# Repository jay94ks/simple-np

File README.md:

# Simple Number Pad

### License
* This repository: MIT, partially GPL-v3 due to TFT library.
* TFT library: GPL-v3, [ST7735_TFT_PICO](https://github.com/gavinlyonsrepo/ST7735_TFT_PICO)

### Video

### Schematic

See `hw/pdf/*.pdf` files to read more details.

### Features
* MCU: RP2040, 133MHz Dual core.
* 5 keys for user-defined functions.
* 17 keys for number pad.
* `TFT` display for calculator if no `HID` attached.
* 2 macro control keys, `RECORD` and `PLAY`.

### Plans for future features
* A flash memory to store user configurations? (currently, they're stored at `SRAM` of MCU only, so, volatile)
* I2C or SPI extension port?
* A little game that runs on the `TFT` display?
* Anything else...

### Firmware
Current planed features are implemented.
Now, calculator mode will be implemented soon.

### `tinyusb` RX callback.
Don't use `0.15.0` distribution that included on `pico-sdk`.
Update its branch to above version, then it works perfectly.

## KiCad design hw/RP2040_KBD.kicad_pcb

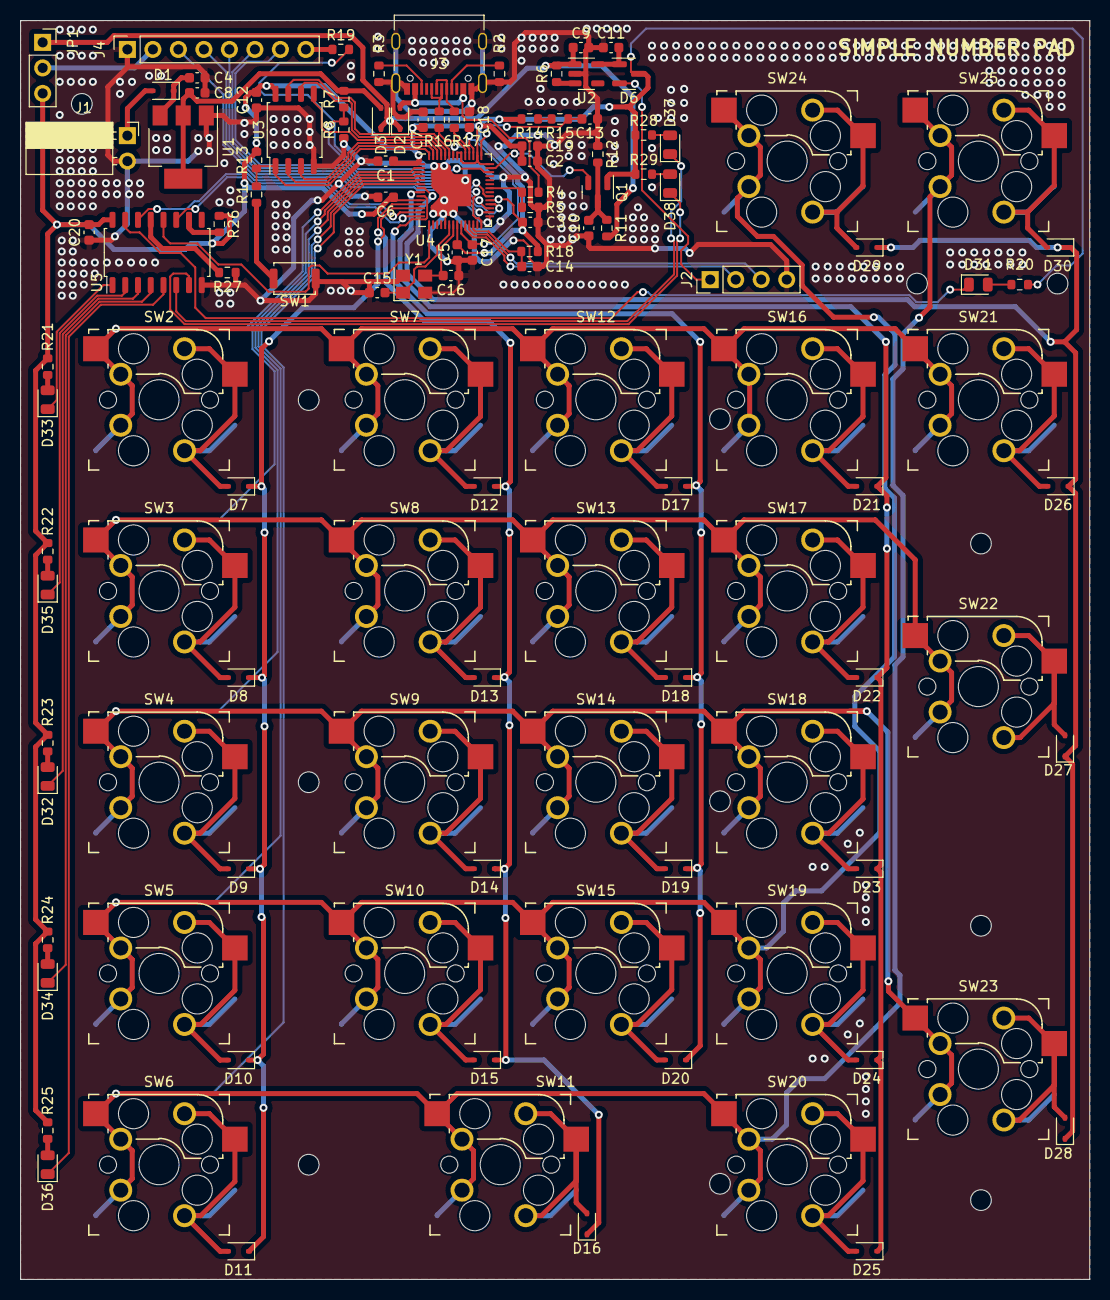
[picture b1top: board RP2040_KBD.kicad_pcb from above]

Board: 2 copper layers, 106.5 x 125.4 mm, 120 parts (0 on the bottom side), 98 nets.

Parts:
C1, C2, C3, C5, C6, C7, C12, C14, C20: 100nF; C_0603_1608Metric
C4, C8, C9, C11: 10uF; C_0603_1608Metric
C10: 1nF; C_0603_1608Metric
C13, C17, C18, C19: 2.2uF; C_0603_1608Metric
C15, C16: 26pF; C_0603_1608Metric
D1, D2, D3: 1N5819WS; D_SOD-323
D6: BAT54C; SOT-23
D7, D8, D9, D10, D11, D12, D13, D14, D15, D16, D17, D18, D19, D20, D21, D22, D23, D24, D25, D26, D27, D28, D29, D30: 1N4148WS; D_SOD-323
D31, D32, D33, D34, D35, D36, D37, D38: LED; LED_0805_2012Metric
J1: BAT_9V; PinSocket_1x02_P2.54mm_Horizontal
J2: SWD; PinHeader_1x04_P2.54mm_Vertical
J3: USB_C_Receptacle_USB2.0; USB_C_Receptacle_Palconn_UTC16-G
J4: TFT_LCD; PinSocket_1x08_P2.54mm_Vertical
JP1: TFT_VCC_SEL; PinSocket_1x03_P2.54mm_Vertical
Q1: 2N7002; SOT-23
R1, R5, R8, R13, R18, R26, R27: 10k; R_0603_1608Metric
R2, R3: 5.1k; R_0603_1608Metric
R4, R7: 5.6k; R_0603_1608Metric
R6, R12: 100k; R_0603_1608Metric
R11: 200k; R_0603_1608Metric
R14: 200; R_0603_1608Metric
R15: 1; R_0603_1608Metric
R16, R17: 6.8; R_0603_1608Metric
R19: 100; R_0603_1608Metric
R20, R21, R22, R23, R24, R25, R28, R29: 1k; R_0603_1608Metric
SW1: SW_Push; SW_Push_SPST_NO_Alps_SKRK
SW2, SW3, SW4, SW5, SW6, SW7, SW8, SW9, SW10, SW11, SW12, SW13, SW14, SW15, SW16, SW17, SW18, SW19, SW20, SW21, SW22, SW23, SW24, SW25: Kailh_socket_MX_optional_reversible
U1: AMS1117-5.0; SOT-223-3_TabPin2
U2: XC6220B331MR; SOT-23-5
U3: W25Q128JVSS; SOIC-8_5.23x5.23mm_P1.27mm
U4: RP2040; QFN-56-1EP_7x7mm_P0.4mm_EP3.2x3.2mm
U5: 74HC595; SOP-16_4.55x10.3mm_P1.27mm
Y1: 12MHz; Crystal_SMD_3225-4Pin_3.2x2.5mm

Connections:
+1V1: C17.2, C18.2, U4.23 (DVDD), U4.45 (VREG_VOUT), U4.50 (DVDD)
+3V3: C1.1, C2.1, C3.1, C5.1, C6.1, C7.1, C12.1, C19.1, C20.2, D6.3, JP1.3 (B), Q1.1 (G), R13.1, R14.1, R18.2, R20.1, R21.1, R22.1, R23.1, R24.1, R25.1, R26.1, R28.1, R29.1, U3.8 (VCC), U4.1 (IOVDD), U4.10 (IOVDD), U4.22 (IOVDD), U4.33 (IOVDD), U4.42 (IOVDD), U4.44 (VREG_IN), U4.48 (USB_VDD), U4.49 (IOVDD), U5.16 (VCC)
+5V: C9.1, D2.1 (K), D3.1 (K), JP1.1 (A), R6.2, R11.2, U2.1 (VIN)
+BATT: C4.1, D1.1 (K), U1.3 (VI)
/MCU/ADC_AVDD: C13.2, R15.2, U4.43 (ADC_AVDD)
/MCU/ADC_VREF: R14.2, R15.1
/MCU/GPIO22: R7.1, R8.2, U4.34 (GPIO22)
/MCU/GPIO24: R4.1, R5.2, U4.36 (GPIO24)
/MCU/GPIO29_ADC3: Q1.2 (S), U4.41 (GPIO29_ADC3)
/MCU/QSPI_SCLK: U3.6 (CLK), U4.52 (QSPI_SCLK)
/MCU/QSPI_SD0: U3.5 (DI(IO0)), U4.53 (QSPI_SD0)
/MCU/QSPI_SD1: U3.2 (DO(IO1)), U4.55 (QSPI_SD1)
/MCU/QSPI_SD2: U3.3 (IO2), U4.54 (QSPI_SD2)
/MCU/QSPI_SD3: U3.7 (IO3), U4.51 (QSPI_SD3)
/MCU/QSPI_SS: R1.1, R13.2, U3.1 (~CS), U4.56 (QSPI_SS)
/MCU/USB_DM: J3.A7 (D-), J3.B7 (D-), R17.1
/MCU/USB_DP: J3.A6 (D+), J3.B6 (D+), R16.1
/TFT_ST7735/TFT_BLK: J4.8, R19.1
/TFT_ST7735/TFT_VCC: J4.2, JP1.2 (C)
BAT_5V: C8.1, D3.2 (A), R7.2, U1.2 (VO)
C5: D26.1 (K), D27.1 (K), D28.1 (K), D29.1 (K), D30.1 (K), U4.7 (GPIO5)
GND: C1.2, C2.2, C3.2, C4.2, C5.2, C6.2, C7.2, C8.2, C9.2, C10.1, C11.1, C12.2, C13.1, C14.2, C15.1, C16.1, C17.1, C18.1, C19.2, C20.1, J1.2, J2.4, J3.A1 (GND), J3.A12 (GND), J3.B1 (GND), J3.B12 (GND), J3.S1 (SHIELD), J4.1, R2.2, R3.1, R5.1, R8.1, R12.1, R27.1, SW1.1, U1.1 (GND), U2.2 (GND), U3.4 (GND), U4.19 (TESTEN), U4.57 (GND), U5.8 (GND), Y1.2, Y1.4
GP0: SW2.1, SW7.1, SW12.1, SW16.1, SW21.1, U4.2 (GPIO0)
GP1: SW3.1, SW8.1, SW13.1, SW17.1, SW22.1, U4.3 (GPIO1)
GP2: SW4.1, SW9.1, SW14.1, SW18.1, SW23.1, U4.4 (GPIO2)
GP3: SW5.1, SW10.1, SW15.1, SW19.1, SW24.1, U4.5 (GPIO3)
GP4: SW6.1, SW11.1, SW20.1, SW25.1, U4.6 (GPIO4)
GP6: D21.1 (K), D22.1 (K), D23.1 (K), D24.1 (K), D25.1 (K), U4.8 (GPIO6)
GP7: D17.1 (K), D18.1 (K), D19.1 (K), D20.1 (K), U4.9 (GPIO7)
GP8: D12.1 (K), D13.1 (K), D14.1 (K), D15.1 (K), D16.1 (K), U4.11 (GPIO8)
GP9: D7.1 (K), D8.1 (K), D9.1 (K), D10.1 (K), D11.1 (K), U4.12 (GPIO9)
GP10: U4.13 (GPIO10), U5.14 (SER)
GP11: U4.14 (GPIO11), U5.11 (SRCLK)
GP12: U4.15 (GPIO12), U5.12 (RCLK)
GP17: J4.7, U4.28 (GPIO17)
GP18: J4.3, U4.29 (GPIO18)
GP19: J4.4, U4.30 (GPIO19)
GP20: J4.6, U4.31 (GPIO20)
GP21: J4.5, U4.32 (GPIO21)
GP28: R19.2, U4.40 (GPIO28_ADC2)
unnamed: D1.2 (A), J1.1
unnamed: D7.2 (A), SW2.2
unnamed: D8.2 (A), SW3.2
unnamed: D9.2 (A), SW4.2
unnamed: D10.2 (A), SW5.2
unnamed: D11.2 (A), SW6.2
unnamed: D12.2 (A), SW7.2
unnamed: D13.2 (A), SW8.2
unnamed: D14.2 (A), SW9.2
unnamed: D15.2 (A), SW10.2
unnamed: D16.2 (A), SW11.2
unnamed: D17.2 (A), SW12.2
unnamed: D18.2 (A), SW13.2
unnamed: D19.2 (A), SW14.2
unnamed: D20.2 (A), SW15.2
unnamed: D21.2 (A), SW16.2
unnamed: D22.2 (A), SW17.2
unnamed: D23.2 (A), SW18.2
unnamed: D24.2 (A), SW19.2
unnamed: D25.2 (A), SW20.2
unnamed: D26.2 (A), SW21.2
unnamed: D27.2 (A), SW22.2
unnamed: D28.2 (A), SW23.2
unnamed: D29.2 (A), SW24.2
unnamed: D30.2 (A), SW25.2
unnamed: D31.2 (A), R20.2
unnamed: D31.1 (K), U5.15 (QA)
unnamed: D32.2 (A), R23.2
unnamed: D32.1 (K), U5.3 (QD)
unnamed: D33.2 (A), R21.2
unnamed: D33.1 (K), U5.1 (QB)
unnamed: D34.2 (A), R24.2
unnamed: D34.1 (K), U5.4 (QE)
unnamed: D35.2 (A), R22.2
unnamed: D35.1 (K), U5.2 (QC)
unnamed: D36.2 (A), R25.2
unnamed: D36.1 (K), U5.5 (QF)
unnamed: D37.2 (A), R28.2
unnamed: D37.1 (K), U5.6 (QG)
unnamed: D38.2 (A), R29.2
unnamed: D38.1 (K), U5.7 (QH)
unnamed: J3.A5 (CC1), R2.1
unnamed: J3.B5 (CC2), R3.2
unnamed: C10.2, Q1.3 (D), R11.1, R12.2
unnamed: R1.2, SW1.2
unnamed: R6.1, U2.3 (CE)
unnamed: C11.2, D6.1, U2.5 (VOUT)
unnamed: R17.2, U4.46 (USB_DM)
unnamed: R16.2, U4.47 (USB_DP)
unnamed: C15.2, U4.20 (XIN), Y1.1
unnamed: C16.2, U4.21 (XOUT), Y1.3
unnamed: R27.2, U5.13 (~OE)
unnamed: R26.2, U5.10 (~SRCLR)
RUN: C14.1, R18.1, U4.26 (RUN)
SWD_3V3: D6.2, J2.1
SWD_CLK: J2.2, U4.24 (SWCLK)
SWD_DIO: J2.3, U4.25 (SWD)
VBUS: D2.2 (A), J3.A4 (VBUS), J3.A9 (VBUS), J3.B4 (VBUS), J3.B9 (VBUS), R4.2

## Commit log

2024-03-04 Initial commit.
2024-03-18 Schematic updated.
2024-03-19 Initial firmware, implements fundamental functionalities.
2024-03-20 FW: implemented simple CDC-based control protocol and corrected numlock LED indicator.
2024-03-23 Implementing TFT display...
2024-03-23 TFT console implemented.
2024-03-23 Update image.
2024-03-23 schematic PDF file updated.
2024-03-23 gerber files are regenerated
2024-03-23 USB-CDC ACM communication implemented for PC application.
2024-03-23 Video and readme.
2024-03-23 FW: refactoring...
2024-03-23 Implemented more complex `IKeyHandler` design to handle keys.
2024-03-23 Added missing `const` keyword.
2024-03-23 Added missing `const_cast` for `Kbd` pointer.
2024-03-24 Key pressing order management improved.
2024-03-24 Added optimize-condition for key handlers.
2024-03-24 Implemented asynchronous framework
2024-03-24 TFT graphic mode implemented.
2024-03-24 Implemented: more deeper abstraction layer to implement macro functionalities.
2024-03-24 switching `fw` and `fw_refactor` files.
2024-03-24 HID report tested.
2024-03-24 few bugs fixed.
2024-03-24 Refactoring completed, but `CDC RX` doesn't work :angry:
2024-03-24 Old firmware codes deletion.
2024-03-24 Some dependency added during debugging
2024-03-25 added `onListen` and `onUnlisten` lifetime methods to let the listener knows.
2024-03-25 Added `_enabled` flag to control keyboard scan-loop.
2024-03-25 solved warnings and added welcome mode to display splash.
2024-03-26 `Welcome` screen's typography time changed.
2024-03-26 `RX` callback problem solved.
